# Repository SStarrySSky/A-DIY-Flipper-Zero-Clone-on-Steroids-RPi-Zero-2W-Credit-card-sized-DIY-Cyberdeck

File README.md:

#   DIY 多功能便携黑客工具（安全研究设备）
```
_____                      ______               
 |  __ \                    |___  /               
 | |__) |_      ___ __   ____  / /  ___ _ __ ___  
 |  ___/\ \ /\ / / '_ \ |_  / / /  / _ \ '__/ _ \ 
 | |     \ V  V /| | | | / / / /__|  __/ | | (_) |
 |_|      \_/\_/ |_| |_|/___/_____/\___|_|  \___/ 
                                                  
 [ Portable Linux-Based Hacking Multi-Tool ]
 [ Powered by RPi Zero 2W | Dual CC1101 | PN532 ]
 ```

> **基于 Raspberry Pi Zero 2W 的 Flipper Zero 开源替代方案**

---

## 免责声明

```
本项目仅供以下用途：
- CTF 竞赛 / 黑客马拉松比赛
- 授权的安全研究与渗透测试
- 教育学习目的

严禁用于任何非法目的！
使用者需自行承担法律责任。
```

---

## 快速导航

| 章节 | 内容 |
|------|------|
| [功能介绍](#功能介绍) | 设备能做什么 |
| [硬件清单](#硬件清单) | 需要购买的材料 |
| [硬件组装](#硬件组装) | 焊接与接线指南 |
| [软件安装](#软件安装) | 系统配置与部署 |
| [使用说明](#使用说明) | 各功能操作方法 |
| [3D外壳](#3d外壳) | 外壳打印指南 |
| [故障排除](#故障排除) | 常见问题解决 |

---

Why settle for a toy when you can carry a workstation? PwnZero isn't just a clone; it's a field-ready pentesting toolkit that fits in your credit-card slot. Built on the 64-bit architecture of Raspberry Pi Zero 2W, it redefines what a handheld hacking multi-tool can do.

## 功能介绍

### 硬件功能

| 模块 | 功能 | 应用场景 |
|------|------|----------|
| **Sub-GHz** | 433/315MHz 信号收发 | 无线门禁、遥控器分析 |
| **NFC** | 读取 NFC/RFID 卡片 | 门禁卡 UID 读取 |
| **Infrared** | 红外信号学习与发送 | 电视/空调遥控 |
| **OLED** | 128x64 显示屏 | 菜单界面显示 |
| **电池** | PiSugar 3 供电 | 便携使用 |

### 软件功能

| 功能 | 说明 |
|------|------|
| 信号录制 | 捕获 Sub-GHz 无线信号 |
| 信号重放 | 重放录制的信号 |
| RollJam 演示 | 滚动码攻击演示 (仅限授权测试) |
| NFC 读卡 | 读取卡片 UID/ATQA/SAK |
| IR 学习 | 学习红外遥控信号 |
| IR 发送 | 发送学习的红外信号 |
| 电量显示 | 实时显示电池电量 |

---

## 硬件清单

### 核心模块

| 组件 | 型号 | 数量 | 参考价格 |
|------|------|------|----------|
| 主控 | Raspberry Pi Zero 2 W | 1 | ~$15 |
| 电源 | PiSugar 3 (1200mAh) | 1 | ~$30 |
| 屏幕 | SH1106 1.3" OLED (I2C) | 1 | ~$5 |
| 无线电 | AS07-M1101D-TH (CC1101) | 2 | ~$6 |
| NFC | PN532 红色小方板 | 1 | ~$8 |
| IR接收 | VS1838B | 1 | ~$1 |
| IR发射 | 940nm LED | 1 | ~$0.5 |
| 按键 | 五向摇杆模块 (带PCB底座) | 1 | ~$2 |
| 状态灯 | 5mm LED (红/黄/绿) | 3 | ~$0.5 |
| 散热片 | 铝制 14x14mm | 1 | ~$1 |
| 摇杆帽 | 五向摇杆帽 | 1 | ~$1 |

### 电阻电容

| 组件 | 规格 | 数量 | 用途 |
|------|------|------|------|
| 电阻 | 330Ω 1/4W | 4 | IR LED + 3个状态灯限流 |
| 电阻 | 10KΩ 1/4W | 5 | 按键上拉 (备用) |
| 电容 | 10uF 16V | 2 | CC1101 电源滤波 |
| 电容 | 100nF (0.1uF) | 2 | CC1101 高频滤波 |

### 辅材

| 组件 | 规格 | 数量 | 用途 |
|------|------|------|------|
| 洞洞板 | 7x5cm 双面镀锡 | 2 | 主板 |
| 漆包线 | 0.5mm | 1卷 | 走线连接 |
| 电烙铁套装 | 含焊锡丝 | 1 | 焊接 |

### 总成本

约 **$70 / ¥350-400**

---

## 硬件组装

### 电压警告

```
⚠️ 重要！接错电压会烧毁模块！

CC1101: 只能接 3.3V (接5V会烧毁)
PN532:  接 5V (模块自带稳压，接3.3V电流不足)
OLED:   接 3.3V
IR:     接 3.3V
```

### GPIO 引脚分配表

| 模块 | 引脚 | GPIO | 物理Pin |
|------|------|------|---------|
| **SH1106 OLED** | | | |
| └ VCC | 3.3V | - | Pin 1 |
| └ GND | GND | - | Pin 9 |
| └ SDA | I2C数据 | GPIO 2 | Pin 3 |
| └ SCL | I2C时钟 | GPIO 3 | Pin 5 |
| **CC1101 TX** | | | |
| └ VCC | 3.3V | - | Pin 17 |
| └ GND | GND | - | Pin 20 |
| └ MOSI | SPI数据出 | GPIO 10 | Pin 19 |
| └ MISO | SPI数据入 | GPIO 9 | Pin 21 |
| └ SCK | SPI时钟 | GPIO 11 | Pin 23 |
| └ CSN | 片选 | GPIO 8 | Pin 24 |
| └ GDO0 | 数据IO | GPIO 13 | Pin 33 |
| **CC1101 RX** | | | |
| └ VCC | 3.3V | - | Pin 17 |
| └ GND | GND | - | Pin 25 |
| └ MOSI | SPI数据出 | GPIO 10 | Pin 19 |
| └ MISO | SPI数据入 | GPIO 9 | Pin 21 |
| └ SCK | SPI时钟 | GPIO 11 | Pin 23 |
| └ CSN | 片选 | GPIO 7 | Pin 26 |
| └ GDO0 | 数据IO | GPIO 19 | Pin 35 |
| └ GDO2 | 状态IO | GPIO 26 | Pin 37 |
| **PN532 NFC** | | | |
| └ VCC | 5V | - | Pin 2 |
| └ GND | GND | - | Pin 6 |
| └ SDA | I2C数据 | GPIO 2 | Pin 3 |
| └ SCL | I2C时钟 | GPIO 3 | Pin 5 |
| **IR 红外** | | | |
| └ TX (LED+330Ω) | 发射 | GPIO 5 | Pin 29 |
| └ RX (VS1838B) | 接收 | GPIO 6 | Pin 31 |
| **五向按键** | | | |
| └ UP | 上 | GPIO 17 | Pin 11 |
| └ DOWN | 下 | GPIO 27 | Pin 13 |
| └ LEFT | 左 | GPIO 22 | Pin 15 |
| └ RIGHT | 右 | GPIO 23 | Pin 16 |
| └ CENTER | 确认 | GPIO 24 | Pin 18 |
| └ COM | 公共端 | GND | Pin 14 |
| **状态 LED** | | | |
| └ LED1 (红+330Ω) | 状态灯1 | GPIO 12 | Pin 32 |
| └ LED2 (黄+330Ω) | 状态灯2 | GPIO 16 | Pin 36 |
| └ LED3 (绿+330Ω) | 状态灯3 | GPIO 20 | Pin 38 |

### 电容接线

```
CC1101 电源滤波 (每个模块都要接):

       ┌─[10uF]──┐
3.3V ──┼─[100nF]─┼── GND
       └─────────┘
```

### IR LED 接线

```
GPIO 5 ──[330Ω]──(+)IR LED(-)── GND
```

### 焊接顺序

1. 给 Pi Zero 焊排针（如果没有）
2. 测试 5V/3.3V 供电正常
3. 焊接 OLED，测试显示
4. 焊接五向按键，测试输入
5. 焊接 CC1101 x2，测试 SPI
6. 焊接 PN532，测试 I2C
7. 焊接 IR 收发，测试红外

### PN532 拨码开关设置

```
设置为 I2C 模式：
SEL0 = 1 (ON)
SEL1 = 0 (OFF)
```

---

## 软件安装

### 1. 系统准备

```bash
# 烧录 Raspberry Pi OS Lite 到 SD 卡
# 启用 SSH、WiFi（用 Raspberry Pi Imager）

# 首次启动后更新系统
sudo apt update && sudo apt upgrade -y
```

### 2. 启用接口

```bash
sudo raspi-config
# Interface Options -> 启用 SPI
# Interface Options -> 启用 I2C
```

### 3. 安装依赖

```bash
sudo apt install -y python3-pip pigpio libnfc-bin libnfc-dev
sudo pip3 install -r requirements.txt
```

### 4. 启动 pigpio 服务

```bash
sudo systemctl enable pigpiod
sudo systemctl start pigpiod
```

### 5. 部署项目

```bash
# 克隆项目
git clone <项目地址> /home/pi/pihacker
cd /home/pi/pihacker

# 运行
sudo python3 main.py
```

### 6. 开机自启（可选）

```bash
sudo cp pihacker.service /etc/systemd/system/
sudo systemctl enable pihacker
```

---

## 使用说明

### 按键操作

| 按键 | 功能 |
|------|------|
| ↑ | 上移菜单 |
| ↓ | 下移菜单 |
| ← | 返回上级 |
| → | (保留) |
| ● | 确认选择 |

### 菜单结构

```
PiHacker
├── Sub-GHz
│   ├── Read Signal    (录制信号)
│   ├── Replay         (重放信号)
│   ├── RollJam Demo   (滚动码演示)
│   └── Set Frequency  (切换频率)
├── NFC
│   ├── Read Card      (读取卡片)
│   └── Emulate Card   (模拟卡片)
├── Infrared
│   ├── Universal Remote (学习遥控)
│   └── Send Power Off   (发送关机)
├── WiFi Tools
│   ├── Scan Networks  (扫描网络)
│   └── Deauth Demo    (断网演示)
└── System
    ├── Device Info    (设备信息)
    ├── Battery Info   (电池信息)
    ├── Reboot         (重启)
    └── Shutdown       (关机)
```

### Sub-GHz 使用

1. 选择 `Read Signal` 开始录制
2. 按下遥控器按钮
3. 录制完成后选择 `Replay` 重放

### NFC 使用

1. 选择 `Read Card`
2. 将卡片贴近 PN532 模块
3. 屏幕显示 UID 信息

### IR 使用

1. 选择 `Universal Remote` 进入学习模式
2. 对准设备按下遥控器
3. 学习完成后可发送信号

---

## 3D外壳

外壳模型文件：`case/pihacker_case.scad`

### 打印参数

| 参数 | 建议值 |
|------|--------|
| 层高 | 0.2mm |
| 填充 | 20% |
| 材料 | PLA |
| 支撑 | 需要 |

### 外壳尺寸

- 外尺寸：80 x 55 x 25 mm
- 壁厚：2mm
- 圆角：3mm

---

## 故障排除

| 问题 | 可能原因 | 解决方法 |
|------|----------|----------|
| OLED 不亮 | I2C 未启用 | `sudo raspi-config` 启用 I2C |
| OLED 不亮 | 接线错误 | 检查 SDA/SCL 是否接反 |
| CC1101 无响应 | SPI 未启用 | `sudo raspi-config` 启用 SPI |
| CC1101 无响应 | CS 引脚冲突 | 确认 TX/RX 用不同 CS |
| NFC 读不到卡 | 拨码开关错误 | 设置为 I2C 模式 |
| NFC 读不到卡 | 供电不足 | 改接 5V |
| IR 无反应 | pigpio 未启动 | `sudo systemctl start pigpiod` |
| 按键不灵 | 接线松动 | 检查焊点 |
| 系统死机 | 3.3V 过载 | PN532 改接 5V |

---

## 项目结构

```
pihacker/
├── main.py              # 主程序入口
├── config.py            # 引脚配置
├── display_manager.py   # OLED 显示管理
├── input_handler.py     # 按键输入处理
├── requirements.txt     # Python 依赖
├── pihacker.service     # systemd 服务
├── modules/
│   ├── subghz.py        # Sub-GHz 模块
│   ├── nfc.py           # NFC 模块
│   ├── infrared.py      # 红外模块
│   └── battery.py       # 电池管理
├── case/
│   └── pihacker_case.scad  # 3D外壳模型
└── README.md            # 本文档
```

---

## 许可证

本项目仅供教育和授权安全研究使用。

---

## 致谢

- Flipper Zero 项目提供的灵感
- Raspberry Pi 基金会
- 开源社区贡献者

---

**再次提醒：请仅在合法授权的场景下使用本设备！**

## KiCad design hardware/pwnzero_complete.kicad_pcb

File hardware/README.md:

# PwnZero PCB 自动生成工具

## 📋 概述

本工具使用Python脚本自动生成完整的KiCad PCB文件，包含：
- ✅ 板框 (85.6mm x 53.98mm)
- ✅ 安装孔 (4个M2.5)
- ✅ 所有元器件及封装
- ✅ 网络定义
- ⚠️ 基础布线（需要在KiCad中完善）

---

## 🚀 快速开始

### 方法一：使用Python脚本自动生成（推荐）

#### 1. 安装依赖

**Windows:**
```bash
# 下载并安装KiCad 7.0+
# https://www.kicad.org/download/

# 将KiCad的bin目录添加到PATH
# 例如: C:\Program Files\KiCad\7.0\bin
```

**Linux:**
```bash
sudo apt update
sudo apt install kicad python3-pcbnew
```

**macOS:**
```bash
brew install kicad
```

#### 2. 运行脚本

```bash
cd hardware
python generate_complete_pcb.py
```

#### 3. 打开生成的PCB

```bash
# 生成的文件: pwnzero_auto.kicad_pcb
# 用KiCad打开即可
```

---

## 📁 文件说明

| 文件 | 说明 | 用途 |
|------|------|------|
| `generate_complete_pcb.py` | Python自动生成脚本 | 生成完整PCB |
| `pwnzero.net` | 网表文件 | 导入立创EDA |
| `pwnzero_bom.csv` | BOM清单 | 元器件采购 |
| `PCB_COMPLETE_DESIGN.md` | 完整设计文档 | 参考资料 |
| `JLCPCB_EDA_IMPORT_GUIDE.md` | 立创EDA导入指南 | 使用立创EDA |

---

## 🔧 方法二：使用立创EDA（在线）

如果不想安装KiCad，可以使用立创EDA在线工具：

### 步骤：

1. **打开立创EDA**
   - 访问 https://lceda.cn/
   - 注册并登录

2. **导入网表**
   - 新建PCB项目
   - 文件 → 导入 → 网表文件
   - 选择 `pwnzero.net`

3. **导入BOM**
   - 工具 → BOM → 导入BOM
   - 选择 `pwnzero_bom.csv`

4. **完成设计**
   - 参考 `JLCPCB_EDA_IMPORT_GUIDE.md` 完成布线
   - 直接下单到嘉立创

详细步骤请查看: `JLCPCB_EDA_IMPORT_GUIDE.md`

---

## 📊 PCB规格

```
尺寸: 85.6mm x 53.98mm (信用卡尺寸)
层数: 2层
板厚: 1.6mm
铜厚: 1oz (35μm)
最小线宽: 0.2mm
最小间距: 0.2mm
阻焊颜色: 黑色（推荐）
字符颜色: 白色
表面处理: HASL无铅
```

---

## 🎯 元器件清单

### 主要模块
- Raspberry Pi Zero 2W x1
- CC1101 Sub-GHz模块 x2 (TX/RX)
- PN532 NFC模块 x1
- SH1106 OLED显示屏 1.3寸 x1
- VS1838B 红外接收器 x1
- 940nm 红外LED x1
- 五向摇杆 x1

### 辅助元件
- 5mm LED (红/黄/绿) x3
- 330Ω 电阻 0805 x4
- 10uF 电容 0805 x2
- 100nF 电容 0805 x2

完整BOM请查看: `pwnzero_bom.csv`

---

## ⚙️ 下一步操作

### 在KiCad中完善PCB

1. **打开文件**
   ```
   用KiCad打开 pwnzero_auto.kicad_pcb
   ```

2. **检查元器件**
   - 确认所有元器件位置正确
   - 调整有冲突的元器件

3. **完成布线**
   - 工具 → 布线 → 自动布线
   - 或手动布线

4. **铺铜**
   - 添加填充区域
   - 网络选择: GND
   - 顶层和底层都铺地

5. **DRC检查**
   - 工具 → 设计规则检查
   - 修复所有错误

6. **生成Gerber**
   - 文件 → 制造输出 → Gerber
   - 压缩成ZIP文件

7. **下单制造**
   - 上传到嘉立创/华秋等PCB厂商
   - 选择参数并下单

---

## 🐛 常见问题

### Q1: 运行脚本报错 "无法导入pcbnew模块"
**A:**
- 确保已安装KiCad 7.0+
- Windows: 将KiCad的bin目录添加到PATH
- Linux: `sudo apt install python3-pcbnew`

### Q2: 元器件封装加载失败
**A:**
- 脚本会跳过无法加载的封装
- 在KiCad中手动添加缺失的元器件
- 或使用立创EDA导入网表

### Q3: 如何修改元器件位置？
**A:**
- 编辑 `generate_complete_pcb.py`
- 修改 `TOP_COMPONENTS` 或 `BOTTOM_COMPONENTS` 中的坐标
- 重新运行脚本

### Q4: 自动布线效果不好？
**A:**
- 脚本只生成基础结构
- 建议在KiCad中手动布线
- 或使用立创EDA的智能布线功能

---

## 📞 技术支持

- **项目文档**: 查看 `PCB_COMPLETE_DESIGN.md`
- **立创EDA指南**: 查看 `JLCPCB_EDA_IMPORT_GUIDE.md`
- **KiCad官方文档**: https://docs.kicad.org/

---

**祝你制作顺利！🎉**

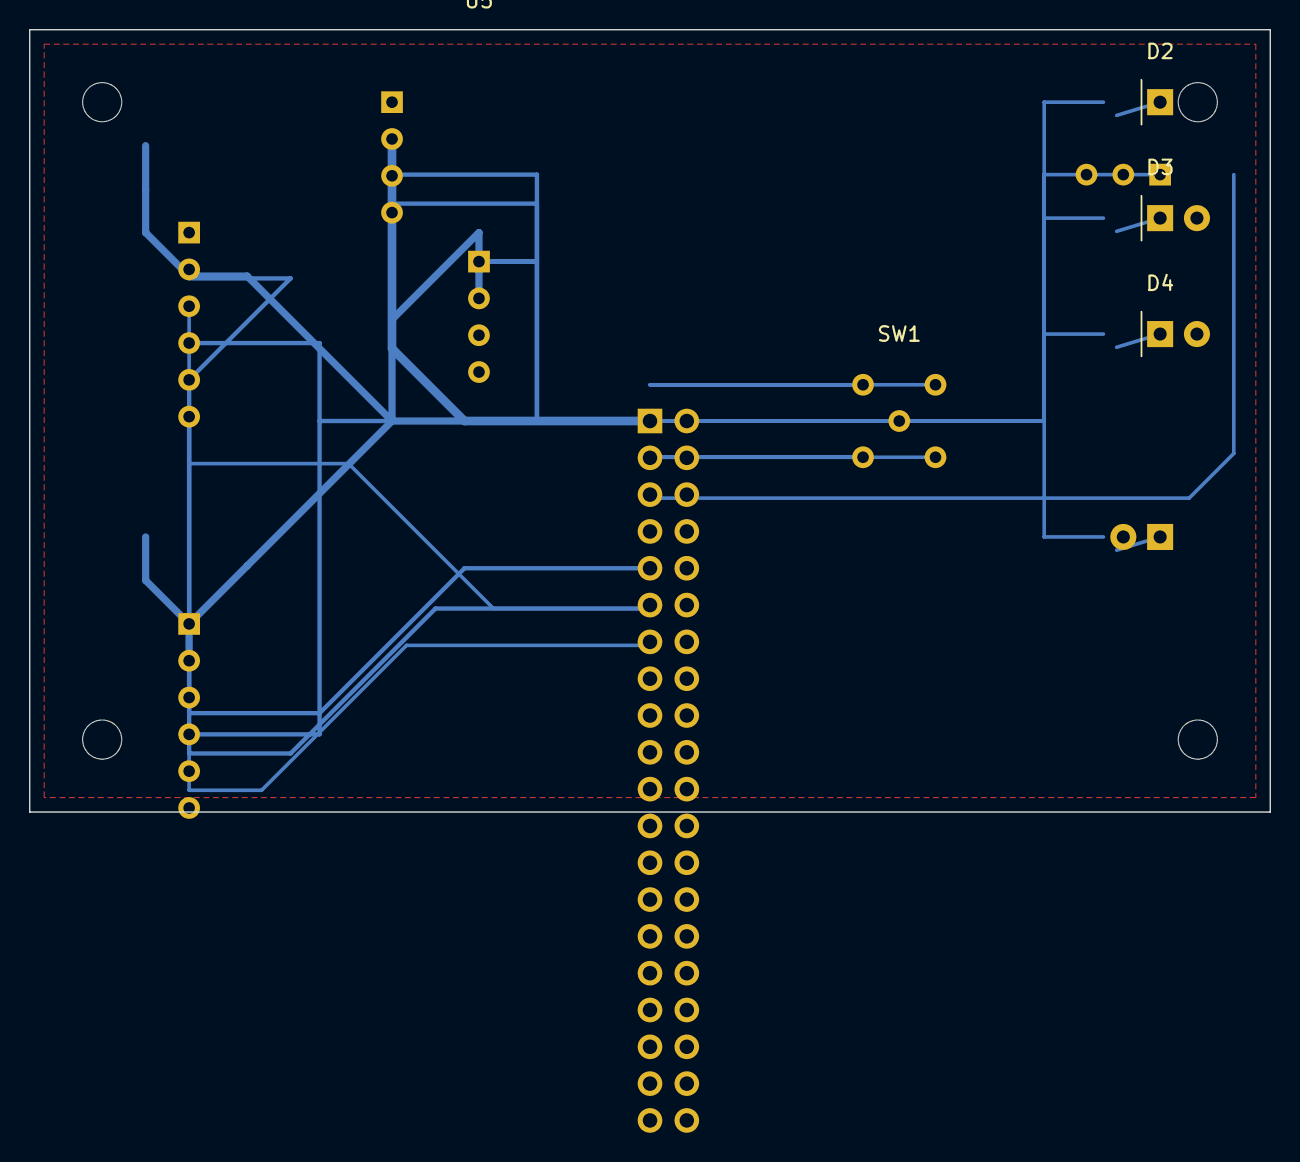
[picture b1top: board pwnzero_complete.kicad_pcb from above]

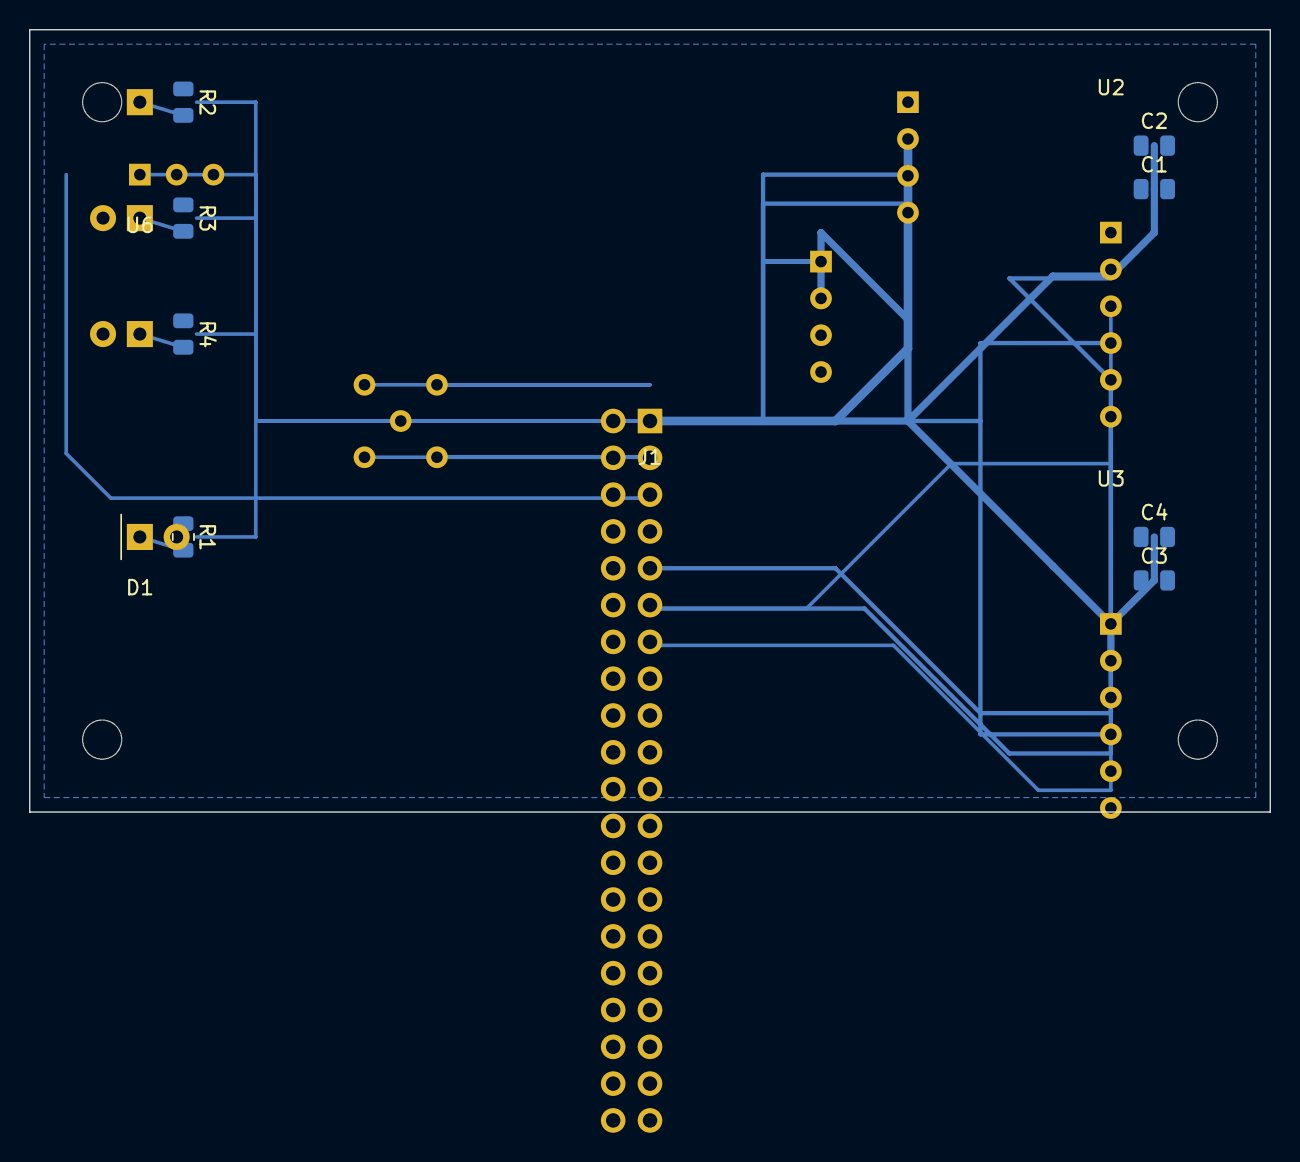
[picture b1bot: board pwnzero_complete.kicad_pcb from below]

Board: 0 copper layers, 85.6 x 54.0 mm, 23 parts (14 on the bottom side), 24 nets.

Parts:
C1, C3: 10uF; C_0805_2012Metric
C2, C4: 100nF; C_0805_2012Metric
D1: IR_LED_940nm; LED_D5.0mm
D2: LED_Red; LED_D5.0mm
D3: LED_Yellow; LED_D5.0mm
D4: LED_Green; LED_D5.0mm
H1, H2, H3, H4: MountingHole; MountingHole_2.7mm_M2.5
J1: RPi_GPIO; PinHeader_2x20_P2.54mm_Vertical
R1, R2, R3, R4: 330; R_0805_2012Metric
SW1: Joystick_5Way; SW_Tactile_SPST_Angled_PTS645Vx58-2LFS
U2: CC1101_TX; CC1101_Module
U3: CC1101_RX; CC1101_Module
U4: PN532; PN532_Module
U5: SH1106; OLED_128x64_I2C
U6: VS1838B; Vishay_MINICAST-3Pin

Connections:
+3V3: C1.1, C2.1, C3.1, C4.1, J1.1, J1.17, U2.2, U3.2, U5.2, U6.3
+5V: J1.2, J1.4, U4.2
CC1101_RX_CS: J1.7, J1.26, U3.3
CC1101_TX_CS: J1.8, J1.24, U2.3
GND: C1.2, C2.2, C3.2, C4.2, D1.2, D2.2, D3.2, D4.2, J1.6, J1.12, J1.14, J1.15, J1.16, J1.18, J1.20, J1.22, J1.25, J1.27, J1.28, J1.30, J1.34, J1.39, J1.40, U2.1, U3.1, U4.1, U5.1, U6.2
GPIO5_JOY_UP: J1.29, SW1.1
GPIO6_JOY_DOWN: J1.31, SW1.3
GPIO12_LED_RED: J1.32, R2.1
GPIO13_JOY_LEFT: J1.33, SW1.2
GPIO16_LED_YELLOW: J1.36, R3.1
GPIO17_IR_TX: J1.11, R1.1
GPIO19_JOY_RIGHT: J1.35, SW1.4
GPIO20_LED_GREEN: J1.38, R4.1
GPIO26_JOY_CENTER: J1.37, SW1.5
GPIO27_IR_RX: J1.13, U6.1
I2C_SCL: J1.5, U4.4, U5.3
I2C_SDA: J1.3, U4.3, U5.4
LED_GREEN_ANODE: D4.1, R4.2
LED_IR_ANODE: D1.1, R1.2
LED_RED_ANODE: D2.1, R2.2
LED_YELLOW_ANODE: D3.1, R3.2
SPI_MISO: J1.9, J1.21, U2.6, U3.6
SPI_MOSI: J1.10, J1.19, U2.4, U3.4
SPI_SCLK: J1.23, U2.5, U3.5

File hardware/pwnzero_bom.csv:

Comment,Designator,Footprint,LCSC Part Number,Manufacturer,Manufacturer Part,Quantity,Value
"Main Controller - 1GHz Quad-core ARM Cortex-A53",U1,RPi_Zero_2W,,Raspberry Pi Foundation,Raspberry Pi Zero 2W,1,Raspberry_Pi_Zero_2W
"Sub-GHz Transceiver TX - 433/315MHz",U2,CC1101_Module,,Texas Instruments,CC1101,1,CC1101_TX
"Sub-GHz Transceiver RX - 433/315MHz",U3,CC1101_Module,,Texas Instruments,CC1101,1,CC1101_RX
"NFC/RFID Module - 13.56MHz I2C Address: 0x24",U4,PN532_Module,C84849,NXP,PN532,1,PN532
"OLED Display 1.3 inch 128x64 I2C Address: 0x3C",U5,OLED_128x64,C88334,,SH1106 1.3inch OLED,1,SH1106
"IR Receiver 38kHz",U6,TO-92,C10677,Vishay,VS1838B,1,VS1838B
"5-Way Navigation Switch",SW1,Joystick_5Way,C318884,,5-Way Tactile Switch,1,5Way_Joystick
"IR LED 940nm for IR transmission",D1,LED_D5.0mm,C72041,Everlight,IR333C,1,IR_LED_940nm
"Status LED Red",D2,LED_D5.0mm,C84256,Hubei KENTO,C5-R,1,LED_Red
"Status LED Yellow",D3,LED_D5.0mm,C84259,Hubei KENTO,C5-Y,1,LED_Yellow
"Status LED Green",D4,LED_D5.0mm,C84257,Hubei KENTO,C5-G,1,LED_Green
"Current limiting resistor for IR LED",R1,R_0805,C17630,UNI-ROYAL,0805W8F3300T5E,1,330
"Current limiting resistor for LED Red",R2,R_0805,C17630,UNI-ROYAL,0805W8F3300T5E,1,330
"Current limiting resistor for LED Yellow",R3,R_0805,C17630,UNI-ROYAL,0805W8F3300T5E,1,330
"Current limiting resistor for LED Green",R4,R_0805,C17630,UNI-ROYAL,0805W8F3300T5E,1,330
"Power filter capacitor for CC1101 TX",C1,C_0805,C15850,Samsung,CL21A106KAYNNNE,1,10uF
"High-freq filter capacitor for CC1101 TX",C2,C_0805,C49678,YAGEO,CC0805KRX7R9BB104,1,100nF
"Power filter capacitor for CC1101 RX",C3,C_0805,C15850,Samsung,CL21A106KAYNNNE,1,10uF
"High-freq filter capacitor for CC1101 RX",C4,C_0805,C49678,YAGEO,CC0805KRX7R9BB104,1,100nF

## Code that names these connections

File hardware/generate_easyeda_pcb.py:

#!/usr/bin/env python3
"""
PwnZero - 立创EDA PCB自动生成脚本
生成完整的立创EDA JSON格式PCB文件，包含元器件、封装、布线
"""

import json
import math

# PCB基本参数
PCB_WIDTH = 85.6  # mm
PCB_HEIGHT = 53.98  # mm
LAYER_COUNT = 2

# 元器件坐标定义（顶层）
TOP_COMPONENTS = {
    "U5": {"name": "OLED_SH1106", "x": 31, "y": 16, "rotation": 0, "layer": "TopLayer"},
    "SW1": {"name": "Joystick_5Way", "x": 60, "y": 27, "rotation": 0, "layer": "TopLayer"},
    "D2": {"name": "LED_Red", "x": 78, "y": 5, "rotation": 0, "layer": "TopLayer"},
    "D3": {"name": "LED_Yellow", "x": 78, "y": 13, "rotation": 0, "layer": "TopLayer"},
    "D4": {"name": "LED_Green", "x": 78, "y": 21, "rotation": 0, "layer": "TopLayer"},
}

# 元器件坐标定义（底层）
BOTTOM_COMPONENTS = {
    "U1": {"name": "RPi_Zero_2W", "x": 42.8, "y": 27, "rotation": 0, "layer": "BottomLayer"},
    "U2": {"name": "CC1101_TX", "x": 11, "y": 14, "rotation": 0, "layer": "BottomLayer"},
    "U3": {"name": "CC1101_RX", "x": 11, "y": 41, "rotation": 0, "layer": "BottomLayer"},
    "U4": {"name": "PN532", "x": 45, "y": 27, "rotation": 0, "layer": "BottomLayer"},
    "U6": {"name": "VS1838B", "x": 78, "y": 10, "rotation": 180, "layer": "BottomLayer"},
    "D1": {"name": "IR_LED", "x": 78, "y": 35, "rotation": 180, "layer": "BottomLayer"},
    "R1": {"name": "R_330", "x": 75, "y": 35, "rotation": 90, "layer": "BottomLayer"},
    "R2": {"name": "R_330", "x": 75, "y": 5, "rotation": 90, "layer": "BottomLayer"},
    "R3": {"name": "R_330", "x": 75, "y": 13, "rotation": 90, "layer": "BottomLayer"},
    "R4": {"name": "R_330", "x": 75, "y": 21, "rotation": 90, "layer": "BottomLayer"},
    "C1": {"name": "C_10uF", "x": 8, "y": 11, "rotation": 0, "layer": "BottomLayer"},
    "C2": {"name": "C_100nF", "x": 8, "y": 8, "rotation": 0, "layer": "BottomLayer"},
    "C3": {"name": "C_10uF", "x": 8, "y": 38, "rotation": 0, "layer": "BottomLayer"},
    "C4": {"name": "C_100nF", "x": 8, "y": 35, "rotation": 0, "layer": "BottomLayer"},
}

# 网络连接定义
NETS = {
    "GND": [],
    "+3V3": [],
    "+5V": [],
    "I2C_SDA": [("U1", "GPIO2"), ("U4", "SDA"), ("U5", "SDA")],
    "I2C_SCL": [("U1", "GPIO3"), ("U4", "SCL"), ("U5", "SCL")],
    "SPI_MOSI": [("U1", "GPIO10"), ("U2", "MOSI"), ("U3", "MOSI")],
    "SPI_MISO": [("U1", "GPIO9"), ("U2", "MISO"), ("U3", "MISO")],
    "SPI_SCLK": [("U1", "GPIO11"), ("U2", "SCK"), ("U3", "SCK")],
    "CC1101_TX_CS": [("U1", "GPIO8"), ("U2", "CS")],
    "CC1101_RX_CS": [("U1", "GPIO7"), ("U3", "CS")],
    "GPIO5_IR_TX": [("U1", "GPIO5"), ("R1", "1")],
    "GPIO6_IR_RX": [("U1", "GPIO6"), ("U6", "OUT")],
    "GPIO12_LED_RED": [("U1", "GPIO12"), ("R2", "1")],
    "GPIO16_LED_YELLOW": [("U1", "GPIO16"), ("R3", "1")],
    "GPIO20_LED_GREEN": [("U1", "GPIO20"), ("R4", "1")],
}

def mm_to_mil(mm):
    """毫米转密尔（立创EDA使用密尔作为单位）"""
    return mm * 39.3701

def generate_board_outline():
    """生成板框"""
    width_mil = mm_to_mil(PCB_WIDTH)
    height_mil = mm_to_mil(PCB_HEIGHT)

    outline = {
        "gge": "TRACK",
        "layerid": "19",  # Board Outline layer
        "net": "",
        "pointArr": [
            {"x": 0, "y": 0},
            {"x": width_mil, "y": 0},
            {"x": width_mil, "y": height_mil},
            {"x": 0, "y": height_mil},
            {"x": 0, "y": 0}
        ],
        "strokeWidth": 1
    }
    return outline

def generate_mounting_holes():
    """生成安装孔"""
    holes = []
    positions = [
        (5, 5),
        (80.6, 5),
        (5, 48.98),
        (80.6, 48.98)
    ]

    for i, (x, y) in enumerate(positions):
        hole = {
            "gge": "PAD",
            "layerid": "11",
            "net": "",
            "x": mm_to_mil(x),
            "y": mm_to_mil(y),
            "width": mm_to_mil(2.7),
            "height": mm_to_mil(2.7),
            "holeR": mm_to_mil(2.7),
            "shape": "ROUND",
            "id": f"H{i+1}"
        }
        holes.append(hole)

    return holes

def generate_component_footprint(ref, comp_data):
    """生成元器件封装"""
    x_mil = mm_to_mil(comp_data["x"])
    y_mil = mm_to_mil(comp_data["y"])

    footprint = {
        "gge": "LIB",
        "layerid": "1" if comp_data["layer"] == "TopLayer" else "2",
        "x": x_mil,
        "y": y_mil,
        "rotation": comp_data["rotation"],
        "id": ref,
        "name": comp_data["name"],
        "pads": []
    }

    return footprint

print("正在生成立创EDA PCB文件...")
print("第1部分：基础结构")
